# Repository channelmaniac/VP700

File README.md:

# VP700
RCA VP700 Tiny BASIC Card

This was a project by the late Ed Keefe. He had dumped the VP700 Tiny BASIC card from RCA for the COSMAC VIP computer, reverse engineered the schematic from the board, and built a PCB to try and reproduce the card. The original can be seen on his web site at: https://www.cosmacvip.com/GALLERY/LARGEWM/IMG_2589.jpg

I was given a copy of the gerbers and had some PCBs made but could not get his PCB working. The problem boiled down to timing, address decoding, and which signals got used where. I figured out one part of it but was stuck getting it to boot immediately to the card after a reset of the CPU. Walter Miraglia was very helpful in working with me on this he engaged Josh Bensadon who figured out the issues, the proper connections for each part of the signalling, and that a tiny capacitor was needed to stretch a pulse on the /MRD (Memory Read) line.

Based on Josh's changes, I laid out a new card using Ed's logo like his had plus his name, which, additionally, I'd like to extend many thanks to Con Skordis for help with the 44 pin edge connector in KiCAD. With his permission I have added the edge connector files for KiCAD into the KiCAD Template directory here.

There are some difficulties in designing for this system. The address bus is multiplexed with the TPA signal used to define when the lower address bus information is available then when the upper address bus information is. The 8000 signal is a flipped version of the /8000 used to access the monitor ROM. When the 8000 signal is low, the lower half of memory is addressed. The lower half of memory is RAM and is incompletely decoded for access, resulting in mirrors at every 4K for the lower half of memory. The RAM can be disabled by asserting the MINH signal on the expansion bus, taking it to logic High. The Tiny BASIC card makes use of this.

The Tiny BASIC card represented some challenges as the Mask ROMs from RCA not only latch the address information internally, they also have internal address decoding so no external ICs for decoding addresses were necessary on that card. The 4516 CMOS chip is a 4 to 16 decoder and while it could be used to decode the addresses for the ROMs, it wasn't. It was used to decode the RAM address, disable the RAM from 0000-0FFF, and enable only the bank of RAM from 1000-1FFF using the MINH line. This is because the Tiny BASIC code sits at 0000-0FFF in memory and would otherwise conflict with the RAM. The diode on the MINH signal is because RCA specified a diode to be used on that signal line in documentation. To further the difficulty in understanding how this card works, the upper address lines are not used in order for inputs on the 4516. Instead of mapping the inputs D(A15), C(A14), B(A13), and A(A12) being used, RCA mapped them as D(A15), C(A13), B(A12), and A(A14). This means you must build a table to map the upper address lines to understand the outputs properly.

Lower Memory Map:  (NOTE: the upper half of memory exhibits the same mirroring behavior with the Monitor ROM.)

0000-03FF - Bank 0 RAM (2x 2114 RAM chips)

0400-07FF - Bank 1 RAM (2x 2114 RAM chips)

0800-0BFF - Bank 2 RAM (2x 2114 RAM chips)

0C00-0FFF - Bank 3 RAM (2x 2114 RAM chips)

1000-1FFF - Mirror of bank 0-3

2000-2FFF - Mirror of bank 0-3

3000-3FFF - Mirror of bank 0-3

4000-4FFF - Mirror of bank 0-3

5000-5FFF - Mirror of bank 0-3

6000-6FFF - Mirror of bank 0-3

7000-7FFF - Mirror of bank 0-3

This new card uses the 4516 to also decode the address for the EEPROM / EPROM used to hold the Tiny BASIC code to have it appear in memory from 0000-0FFF so the only additional chip needed is the 74HC573 to latch the
upper 8 address lines. The card calls for a single 28C256 but the upper address lines are grounded. You are only using the lower 4K. If a 28C256 can't be found, a simple 27C64 will work just fine.

A 74HCT573 Octal latch will also work if you have those on hand instead of a 74HC573. Additionally a 74HC574 or 74HCT574 octal flip-flop will also work if a 573 is hard to source. While 74LS/S/AS/etc. may work, those
are NOT recommended as they take too much current to drive the inputs. RCA calls out that you should use CMOS buffers to drive TTL loads on the expansion interface and this card does not use those.

Thanks to Walter Miraglia for the page scans of the RCA Tiny BASIC manual. I've put them together in a single PDF file and put them here to make things easy.

The Tiny BASIC ROM code is as simple as installing the EMMA 02 emulator and grabbing the VP700_Tiny_BASIC.bin file from it to program into your own IC.

The PCBs have been ordered through JLCPCB and verified by me before the files were uploaded to this repsitory.

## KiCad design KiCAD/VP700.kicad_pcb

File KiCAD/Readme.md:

These are the KiCAD files for the VP700 circuit board. Please let me know if you have any feedback.

Yes, there is only 1 .1uf cap on the PCB. This was just echoing how RCA did the original PCB back in the day
as it only had 1 .1uf cap on it.

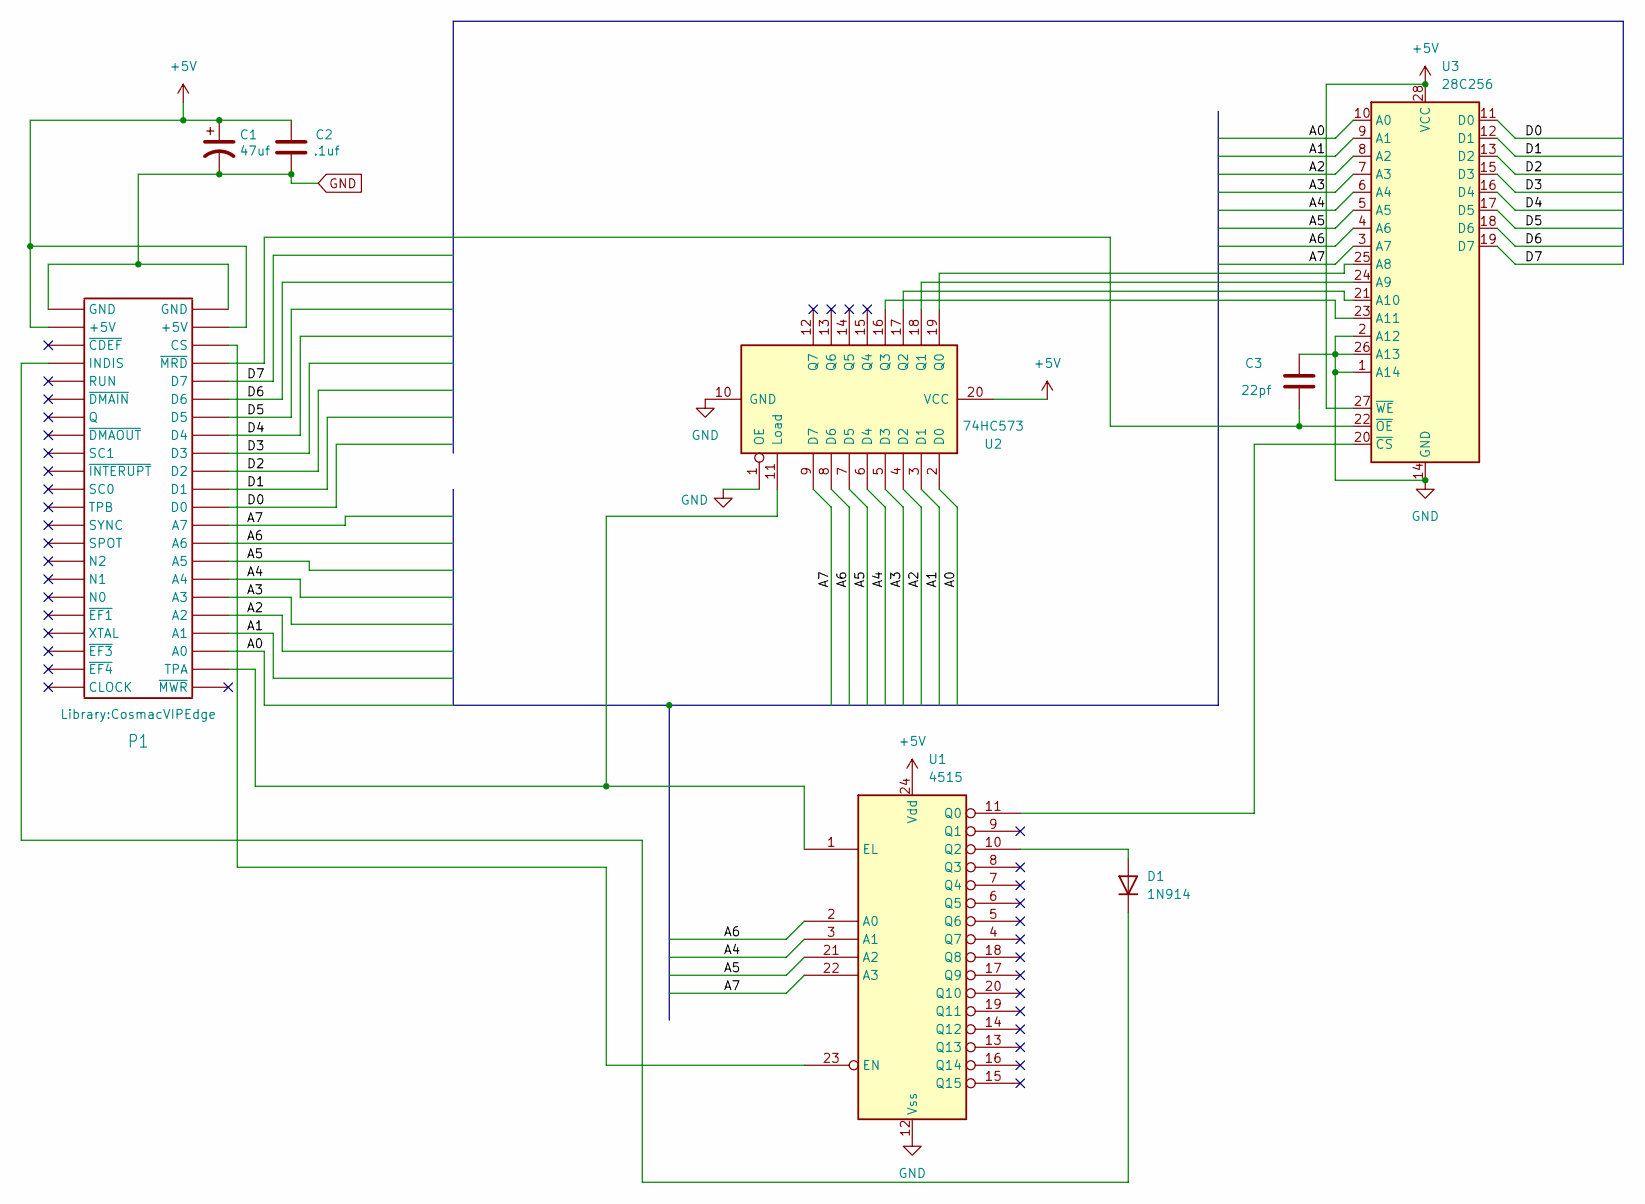
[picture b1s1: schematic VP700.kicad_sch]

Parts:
C1: 47uf; C_Radial_D8.0mm_H7.0mm_P3.50mm
C2: .1uf; C_Disc_D3.0mm_W1.6mm_P2.50mm
C3: 22pf; C_Disc_D3.0mm_W1.6mm_P2.50mm
D1: 1N914; D_DO-35_SOD27_P7.62mm_Horizontal
P1: Cosmac VIP Edge; CosmacVIPEdge
U1: 4515; DIP-24_18.0mmx34.29mm_W15.24mm_LongPads
U2: 74HC573; DIP-20_W7.62mm_LongPads
U3: 28C256; DIP-28_W15.24mm_LongPads

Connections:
+5V: C1.1, C2.1, P1.21 (+5V), P1.Y (+5V), U1.24 (Vdd), U2.20 (VCC), U3.27 (~WE), U3.28 (VCC)
/A0: P1.C (A0), U2.2 (D0), U3.10 (A0)
/A1: P1.D (A1), U2.3 (D1), U3.9 (A1)
/A2: P1.E (A2), U2.4 (D2), U3.8 (A2)
/A3: P1.F (A3), U2.5 (D3), U3.7 (A3)
/A4: P1.H (A4), U1.3 (A1), U2.6 (D4), U3.6 (A4)
/A5: P1.J (A5), U1.21 (A2), U2.7 (D5), U3.5 (A5)
/A6: P1.K (A6), U1.2 (A0), U2.8 (D6), U3.4 (A6)
/A7: P1.L (A7), U1.22 (A3), U2.9 (D7), U3.3 (A7)
/D0: P1.M (D0), U3.11 (D0)
/D1: P1.N (D1), U3.12 (D1)
/D2: P1.P (D2), U3.13 (D2)
/D3: P1.R (D3), U3.15 (D3)
/D4: P1.S (D4), U3.16 (D4)
/D5: P1.T (D5), U3.17 (D5)
/D6: P1.U (D6), U3.18 (D6)
/D7: P1.V (D7), U3.19 (D7)
GND: C1.2, C2.2, C3.1, P1.22 (GND), P1.Z (GND), U1.12 (Vss), U2.1 (OE), U2.10 (GND), U3.1 (A14), U3.2 (A12), U3.14 (GND), U3.26 (A13)
unnamed: D1.2 (A), U1.10 (Q2)
unnamed: D1.1 (K), P1.19 (INDIS)
unnamed: P1.X (CS), U1.23 (EN)
unnamed: P1.B (TPA), U1.1 (EL), U2.11 (Load)
unnamed: C3.2, P1.W (~MRD), U3.22 (~OE)
unnamed: U1.11 (Q0), U3.20 (~CS)
unnamed: U2.19 (Q0), U3.25 (A8)
unnamed: U2.18 (Q1), U3.24 (A9)
unnamed: U2.17 (Q2), U3.21 (A10)
unnamed: U2.16 (Q3), U3.23 (A11)

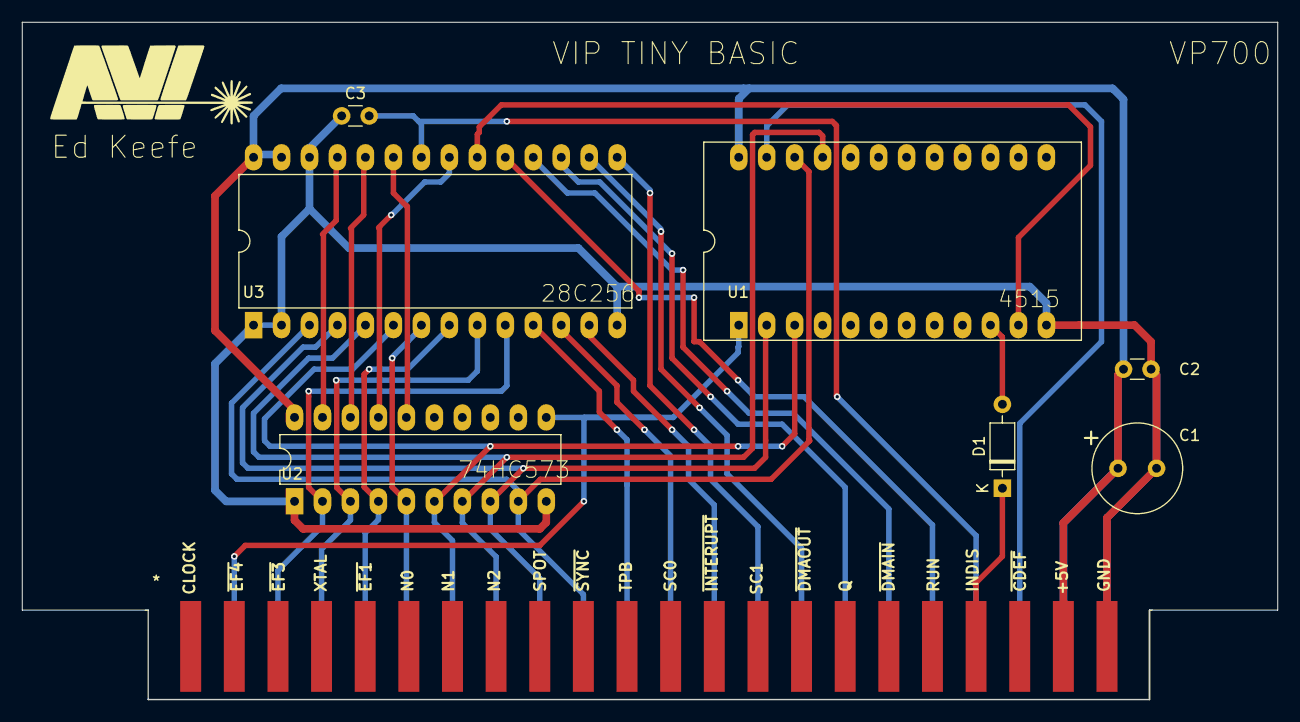
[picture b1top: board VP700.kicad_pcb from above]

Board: 2 copper layers, 113.9 x 61.5 mm, 8 parts (0 on the bottom side), 28 nets.

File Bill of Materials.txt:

Bill of Materials:

This will be short as the card is not complicated! Part numbers not included as I had all the
parts in my stash except for the HC573 which came from Mouser. I have an affinity to use 
Mouser for my parts needs as I live a 45 minute drive from them and get parts next day if I 
order early enough. 

Parts needed: 

1x MC14515 or equivalent 4-bit transpare latch/4-to-16 line decoder
1x 74HC573 Octal D-type latch with 3-state outputs
  OR 74HCT573 Ocal D-type latch with 3-state outputs
1x 28C256 32K x 8 EEPROM 
  OR 28C64 8K x 8 EEPROM
  OR 27C64 8K x 8 EPROM
  OR 2764 8K x 8 EPROM
1x 1N914 / 1N4148 Diode
1x 18-22pf Ceramic (disk or MLCC) capacitor
1x 100nf / .1uf / 104 Ceramic (disk or MLCC) capacitor
1x 100uf Electrolytic capacitor
1x 24-pin .6" wide dual wipe socket
1x 24-pin .6" wide dual wipe socket
1x 20-pin dual wipe socket

And 1 of the PCBs from your favorite PCB manufacturer. I used JLCPCB.

Either the 74HC or HCT family latch will work for this. The important part is that either act as
CMOS inputs with low input current orf 1uA max to keep from being too much of a load to the VIP
which had 1 TTL load listed in the documentation. The outputs for either chip will drive up to 
"15 LSTTL loads" but are only driving the upper address lines to the EEPROM or EPROM being used.

The value of the timing bodge capacitor has been tested at 18pf with a ceramic 1802 CPU installed 
on the VIP and at 22pf with a plastic CPU installed on the VIP. The PCB was designed to use a 
28C256 with the upper address lines grounded. Smaller sized 28 pin devices will work and the 
28C64 and 2764 chips have been successfully tested.

At the slow CPU speeds of the 1802 in the VIP, slower cycle time EPROMs (300ns) have been tested
and should work fine. The 14515 used was from Motorola and the HC573 was from Texas Instruments. 
This should not matter and other manufacturer parts should work fine. Other families (LS, ALS, F,
HCT, etc.) of the HC573 have not been tested. The VIP works at CMOS logic levels but the TTL 
level outputs of the EEPROM/EPROM work fine.

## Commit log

2025-02-20 Update README.md
    Create initial file
2025-02-20 Update README.md
    Fix spacing.
2025-02-20 Add files via upload
    Add gerber view of the card and manual for Tiny BASIC
2025-02-20 Update README.md
    Added in pr0ps on the manual and info on where to get the .bin file to program into the EEPROM / EPROM for the card.
2025-02-20 Add files via upload
    Add KiCAD files
2025-02-20 Rename Readme to Readme.md
2025-02-26 Update Bill of Materials.txt
    Add in the diode...
2025-02-27 Update README.md
    slight change to memory map
2025-03-04 Update Bill of Materials.txt
    74HCT573 added.
2025-03-06 move Readme.md
2025-03-06 Move file
2025-03-06 Update Bill of Materials.txt
    Add in another chip option
2025-03-06 Update README.md
    Minor updates
